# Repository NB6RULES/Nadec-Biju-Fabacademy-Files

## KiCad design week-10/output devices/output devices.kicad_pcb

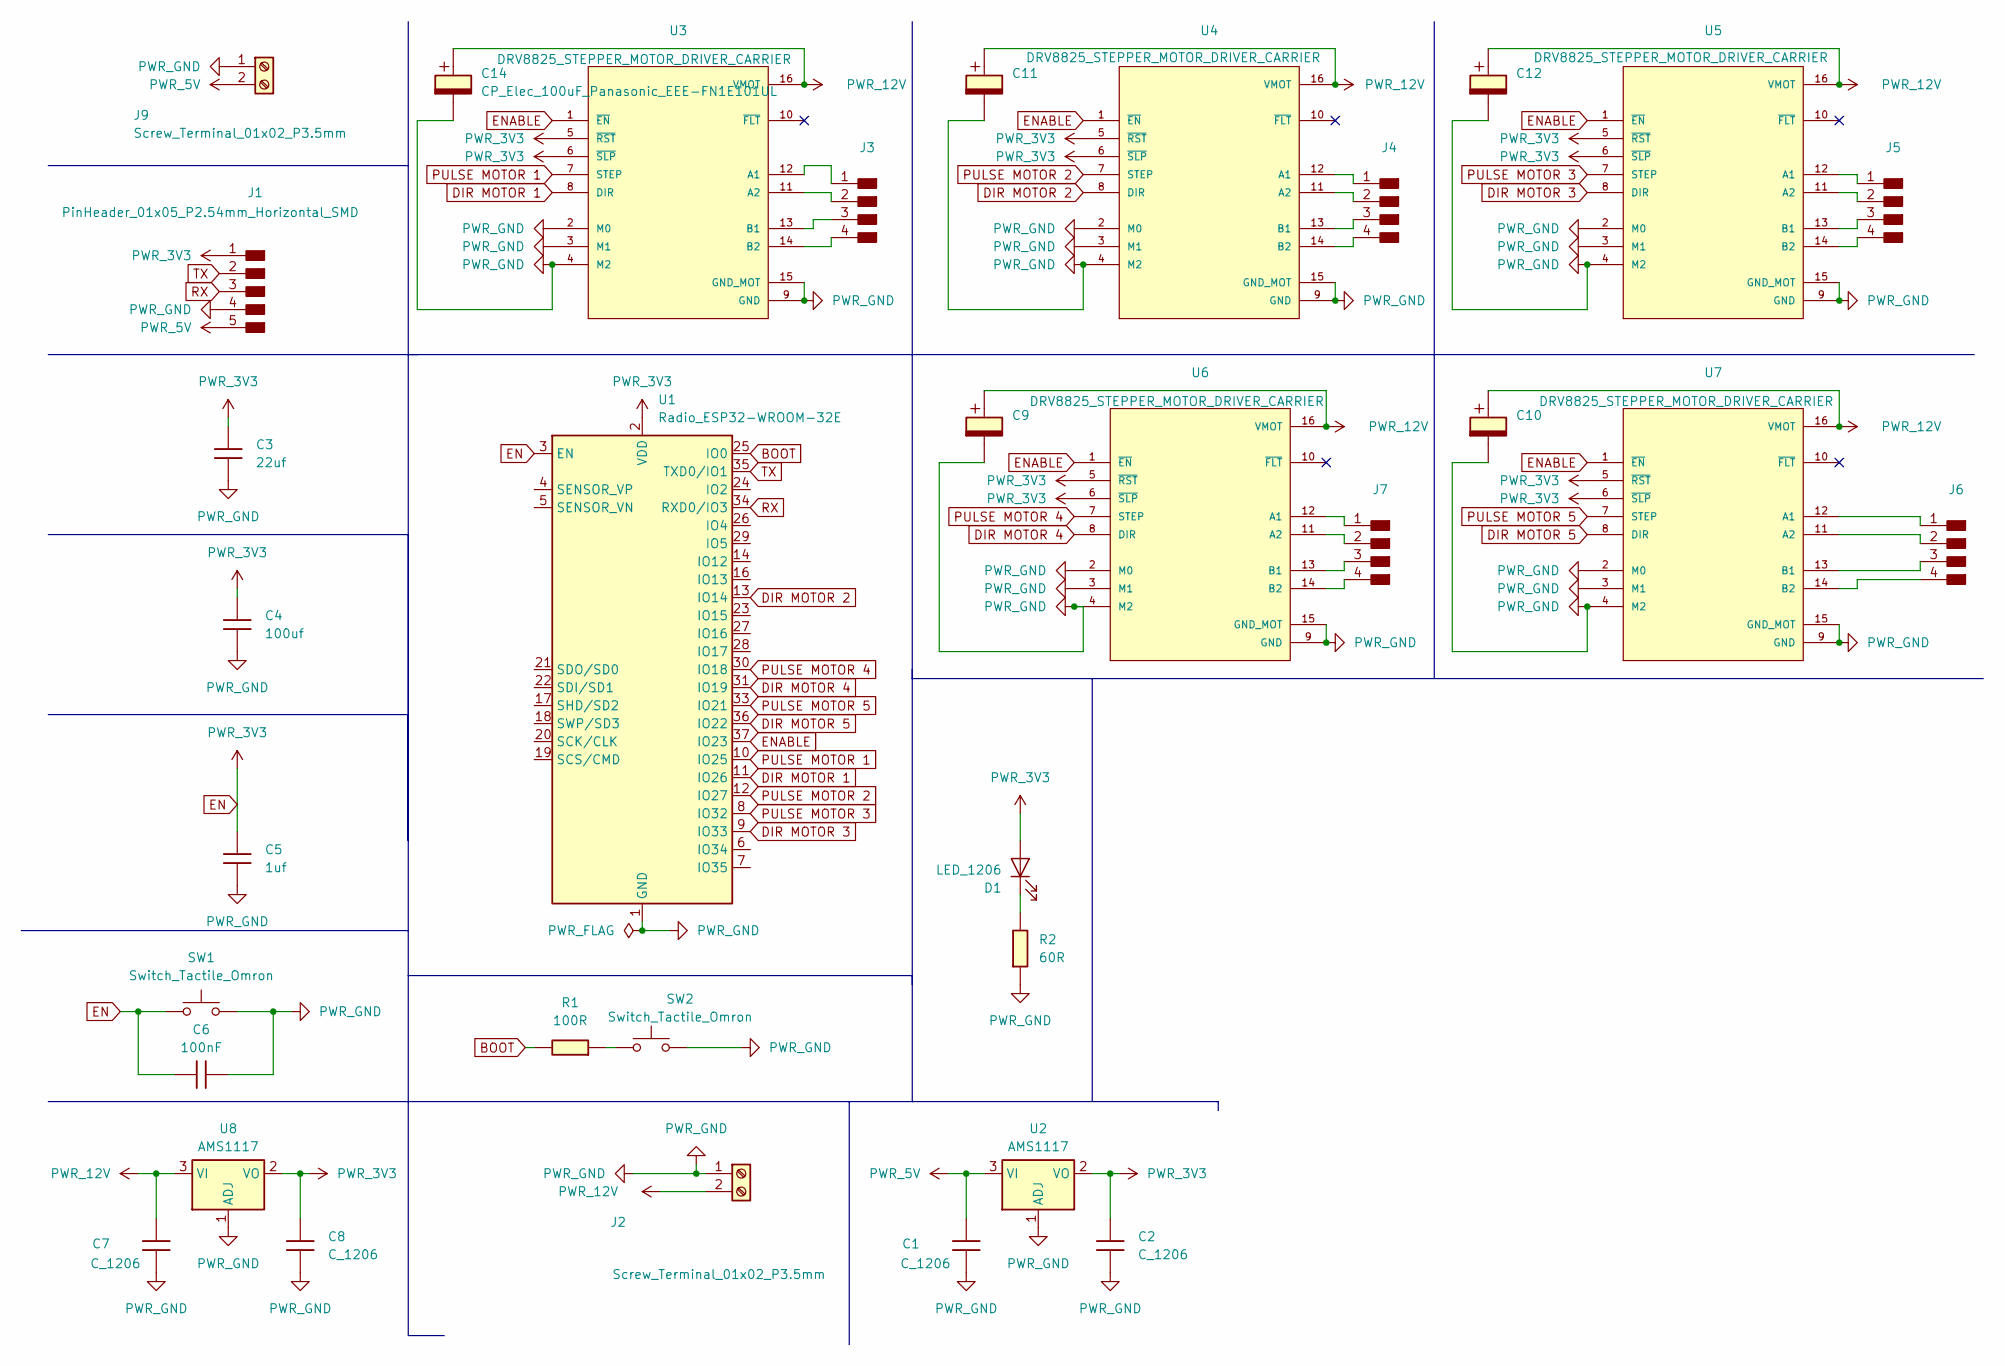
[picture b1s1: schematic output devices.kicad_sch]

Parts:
C1, C2, C7, C8: C_1206
C3: 22uf; C_1206
C4: 100uf; C_1206
C5: 1uf; C_1206
C6: 100nF; C_1206
C9, C10, C11, C12, C14: CP_Elec_100uF_Panasonic_EEE-FN1E101UL; CP_Elec_8x10
D1: LED_1206
J1: PinHeader_01x05_P2.54mm_Horizontal_SMD
J2, J9: Screw_Terminal_01x02_P3.5mm; TerminalBlock_OnShore_1x02_P3.50mm_Horizontal
J3, J4, J5, J6, J7: PinHeader_01x04_P2.54mm_Horizontal_SMD
R1: 100R; R_1206
R2: 60R; R_1206
SW1, SW2: Switch_Tactile_Omron; Button_Omron_B3SN_6.0x6.0mm
U1: Radio_ESP32-WROOM-32E; ESP32-WROOM-32E
U2, U8: AMS1117; SOT-223-3_TabPin2
U3, U4, U5, U6, U7: DRV8825_STEPPER_MOTOR_DRIVER_CARRIER; IC_DRV8825_STEPPER_MOTOR_DRIVER_CARRIER

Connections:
BOOT: R1.1, U1.25 (IO0)
DIR MOTOR 1: U1.11 (IO26), U3.8 (DIR)
DIR MOTOR 2: U1.13 (IO14), U4.8 (DIR)
DIR MOTOR 3: U1.9 (IO33), U5.8 (DIR)
DIR MOTOR 4: U1.31 (IO19), U6.8 (DIR)
DIR MOTOR 5: U1.36 (IO22), U7.8 (DIR)
EN: C2.1, C3.1, C4.1, C5.1, C6.1, C8.1, D1.2 (A), J1.1, SW1.1, U1.2 (VDD), U1.3 (EN), U2.2 (VO), U3.5 (~RST), U3.6 (~SLP), U4.5 (~RST), U4.6 (~SLP), U5.5 (~RST), U5.6 (~SLP), U6.5 (~RST), U6.6 (~SLP), U7.5 (~RST), U7.6 (~SLP), U8.2 (VO)
ENABLE: U1.37 (IO23), U3.1 (~EN), U4.1 (~EN), U5.1 (~EN), U6.1 (~EN), U7.1 (~EN)
unnamed: D1.1 (K), R2.1
unnamed: J3.1, U3.12 (A1)
unnamed: J3.2, U3.11 (A2)
unnamed: J3.3, U3.13 (B1)
unnamed: J3.4, U3.14 (B2)
unnamed: J4.1, U4.12 (A1)
unnamed: J4.2, U4.11 (A2)
unnamed: J4.3, U4.13 (B1)
unnamed: J4.4, U4.14 (B2)
unnamed: J5.1, U5.12 (A1)
unnamed: J5.2, U5.11 (A2)
unnamed: J5.3, U5.13 (B1)
unnamed: J5.4, U5.14 (B2)
unnamed: J6.1, U7.12 (A1)
unnamed: J6.2, U7.11 (A2)
unnamed: J6.3, U7.13 (B1)
unnamed: J6.4, U7.14 (B2)
unnamed: J7.1, U6.12 (A1)
unnamed: J7.2, U6.11 (A2)
unnamed: J7.3, U6.13 (B1)
unnamed: J7.4, U6.14 (B2)
unnamed: R1.2, SW2.1
PULSE MOTOR 1: U1.10 (IO25), U3.7 (STEP)
PULSE MOTOR 2: U1.12 (IO27), U4.7 (STEP)
PULSE MOTOR 3: U1.8 (IO32), U5.7 (STEP)
PULSE MOTOR 4: U1.30 (IO18), U6.7 (STEP)
PULSE MOTOR 5: U1.33 (IO21), U7.7 (STEP)
PWR_5V: C1.1, J1.5, J9.2, U2.3 (VI)
PWR_12V: C7.1, C9.1, C10.1, C11.1, C12.1, C14.1, J2.2, U3.16 (VMOT), U4.16 (VMOT), U5.16 (VMOT), U6.16 (VMOT), U7.16 (VMOT), U8.3 (VI)
PWR_GND: C1.2, C2.2, C3.2, C4.2, C5.2, C6.2, C7.2, C8.2, C9.2, C10.2, C11.2, C12.2, C14.2, J1.4, J2.1, J9.1, R2.2, SW1.2, SW2.2, U1.1 (GND), U1.15 (GND), U1.38 (GND), U1.39 (GND), U2.1 (ADJ), U3.2 (M0), U3.3 (M1), U3.4 (M2), U3.9 (GND), U3.15 (GND_MOT), U4.2 (M0), U4.3 (M1), U4.4 (M2), U4.9 (GND), U4.15 (GND_MOT), U5.2 (M0), U5.3 (M1), U5.4 (M2), U5.9 (GND), U5.15 (GND_MOT), U6.2 (M0), U6.3 (M1), U6.4 (M2), U6.9 (GND), U6.15 (GND_MOT), U7.2 (M0), U7.3 (M1), U7.4 (M2), U7.9 (GND), U7.15 (GND_MOT), U8.1 (ADJ)
RX: J1.3, U1.34 (RXD0/IO3)
TX: J1.2, U1.35 (TXD0/IO1)

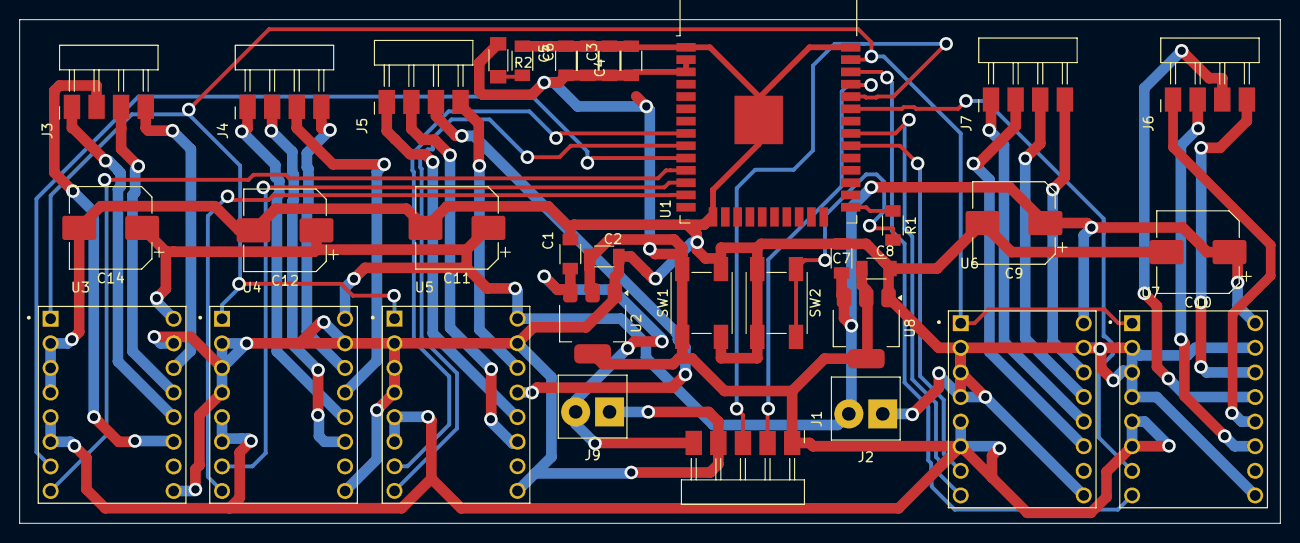
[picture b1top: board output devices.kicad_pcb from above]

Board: 2 copper layers, 130.2 x 52.0 mm, 34 parts (0 on the bottom side), 40 nets.

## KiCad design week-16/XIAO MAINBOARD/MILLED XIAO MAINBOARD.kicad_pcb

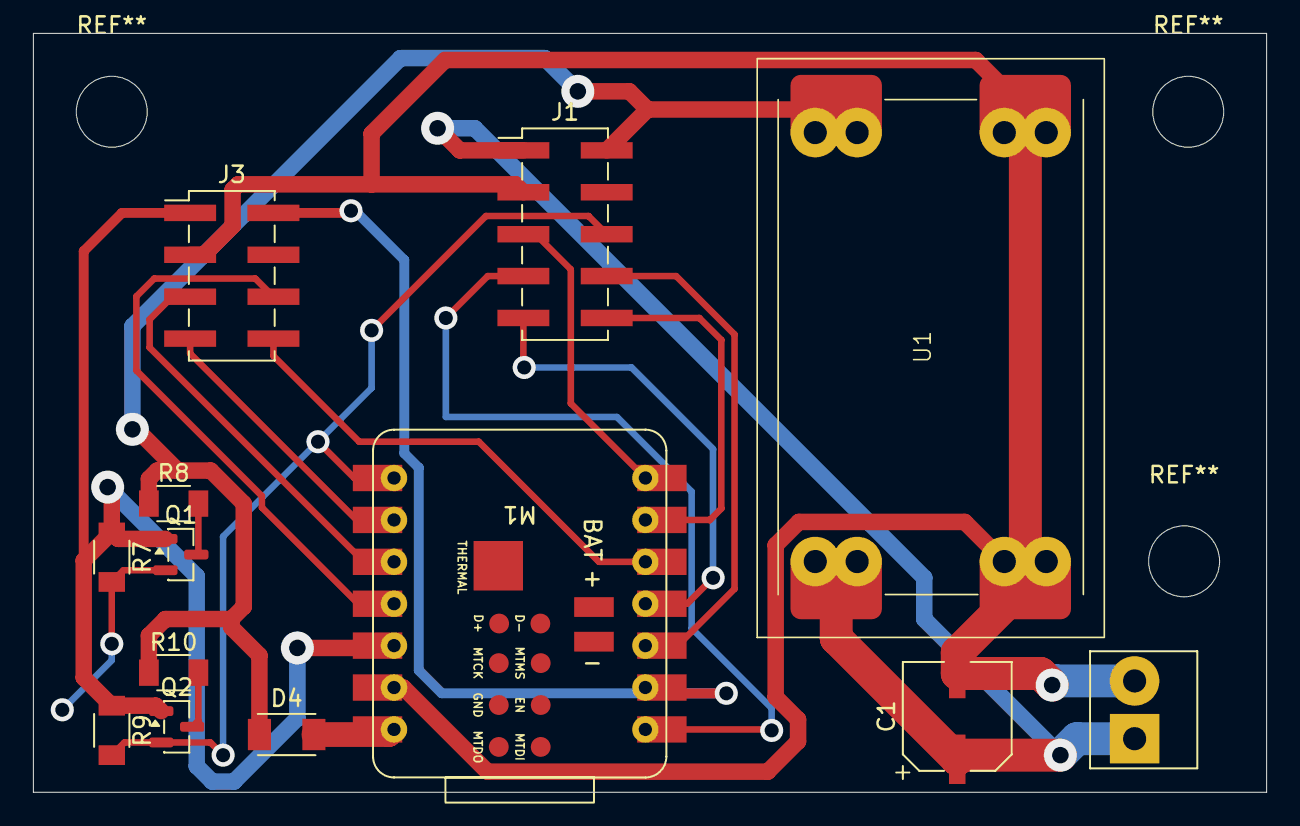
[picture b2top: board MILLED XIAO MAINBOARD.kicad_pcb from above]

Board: 2 copper layers, 74.8 x 46.0 mm, 13 parts (0 on the bottom side), 19 nets.

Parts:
C1: CP_Elec_100uF; CP_Elec_100uF_Panasonic_EEE-FN1E101UL
D4: Diode_Schottky_MiniSMA
J1: PinHeader_02x05_P2.54mm_Vertical_SMD
J2: Screw_Terminal_01x02_P3.5mm; TerminalBlock_OnShore_1x02_P3.50mm_Horizontal
J3: PinHeader_02x04_P2.54mm_Vertical_SMD
M1: Module_XIAO-ESP32S3; SeeedStudio_XIAO_ESP32S3
Q1, Q2: BSS138; SOT-23
R7, R8, R9, R10: 10K; R_1206
U1: Mini560_DCDC_Buck_module

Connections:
3.3v: J3.1, M1.12 (3V3), Q1.1 (G), Q2.1 (G), R7.1, R9.1
5v: D4.2 (A), J1.2, R8.1, R10.1, U1.3 (OUT+)
12v: C1.1, J1.1, J2.1, U1.1 (IN+)
DRAW 1 DIN: Q1.3 (D), R8.2
GND: C1.2, J1.3, J2.2, J3.3, M1.13 (GND), U1.2 (IN-), U1.4 (OUT-)
HALL EFFECT 3 OUT: Q2.3 (D), R10.2
MISO: J3.5, M1.10 (D9)
MOSI: J3.6, M1.11 (D10)
NEOPIXEL DATA: J1.7, M1.1 (D0)
unnamed: D4.1 (K), M1.14 (5V)
RST: J3.2, M1.2 (D1)
RX - BUTTON DOUT: J1.6, M1.8 (D7), Q2.2 (S), R9.2
SCK: J3.7, M1.9 (D8)
SDA: J3.8, M1.5 (D4)
Solenoid 1 Control: J1.8, M1.3 (D2)
Solenoid 2 Control: J1.9, M1.4 (D3)
Solenoid 3 Control: J1.10, M1.6 (D5)
TX - BUTTON DIN: J1.5, M1.7 (D6)
TX - BUTTON DOUT: Q1.2 (S), R7.2

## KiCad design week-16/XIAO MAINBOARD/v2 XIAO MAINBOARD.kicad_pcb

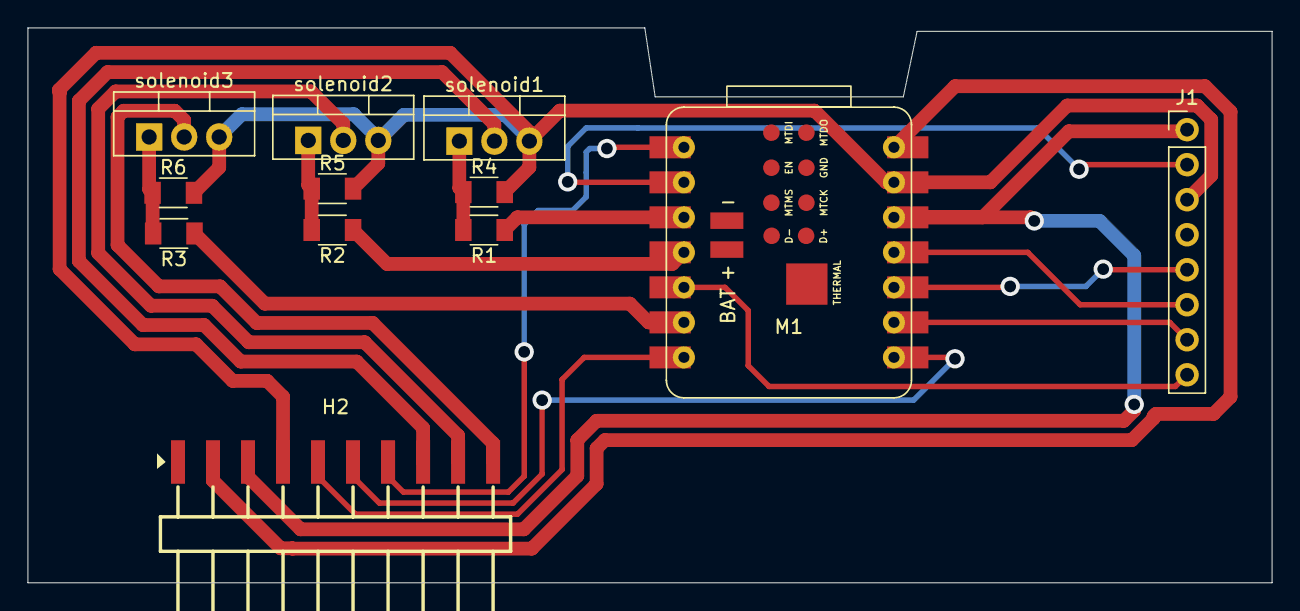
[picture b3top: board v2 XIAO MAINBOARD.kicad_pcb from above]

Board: 2 copper layers, 90.2 x 40.2 mm, 12 parts (0 on the bottom side), 20 nets.

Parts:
H2: HX PZ2.54-1X10P WT; HDR-SMD_10P-P2.54-H-M-W13.3-N
J1: PinHeader_01x08_P2.54mm_Vertical_THT_D1mm
M1: Module_XIAO-ESP32S3; SeeedStudio_XIAO_ESP32S3
R1, R2, R3: 1K; R_1206
R4, R5, R6: 10K; R_1206
solenoid1, solenoid2, solenoid3: IRLZ44N; TO-220-3_Vertical

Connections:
3.3v: H2.3, J1.1, M1.12 (3V3)
5v: H2.2, M1.14 (5V)
GND: H2.4, J1.3, M1.13 (GND), R4.2, R5.2, R6.2, solenoid1.3 (S), solenoid2.3 (S), solenoid3.3 (S)
MISO: J1.5, M1.10 (D9)
MOSI: J1.6, M1.11 (D10)
NEOPIXEL DATA: H2.7, M1.1 (D0)
unnamed: R1.2, R4.1, solenoid1.1 (G)
unnamed: R2.2, R5.1, solenoid2.1 (G)
unnamed: R3.2, R6.1, solenoid3.1 (G)
RST: J1.2, M1.2 (D1)
RX - BUTTON DOUT: H2.6, M1.8 (D7)
SCK: J1.7, M1.9 (D8)
SDA: J1.8, M1.5 (D4)
Solenoid 1: H2.8, solenoid1.2 (D)
Solenoid 1 Control: M1.3 (D2), R1.1
Solenoid 2: H2.9, solenoid2.2 (D)
Solenoid 2 Control: M1.4 (D3), R2.1
Solenoid 3: H2.10, solenoid3.2 (D)
Solenoid 3 Control: M1.6 (D5), R3.1
TX - BUTTON DIN: H2.5, M1.7 (D6)

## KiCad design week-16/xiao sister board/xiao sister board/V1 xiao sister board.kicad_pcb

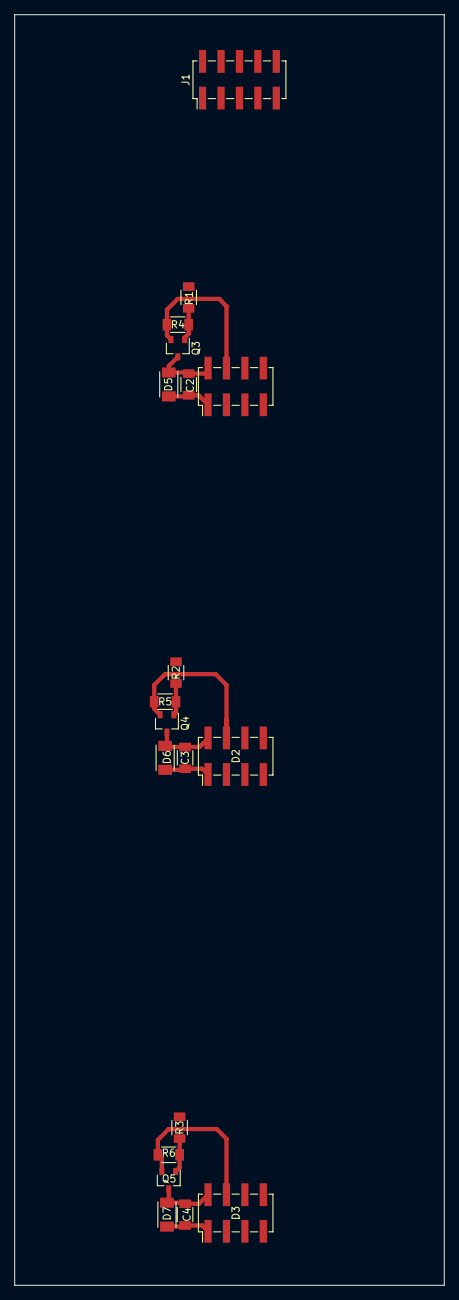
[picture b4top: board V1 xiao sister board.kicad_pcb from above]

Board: 2 copper layers, 59.2 x 175.2 mm, 19 parts (0 on the bottom side), 18 nets.

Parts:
C2, C3, C4: 100nf; C_1206
D1: DRAW 1; PinHeader_02x04_P2.54mm_Vertical_SMD
D2: DRAW 2; PinHeader_02x04_P2.54mm_Vertical_SMD
D3: DRAW 3; PinHeader_02x04_P2.54mm_Vertical_SMD
D5, D6, D7: Diode_Schottky_MiniSMA
J1: PinHeader_02x05_P2.54mm_Vertical_SMD
Q3, Q4, Q5: Transistor_MOSFET_NCh_SOT23; SOT-23-3
R1, R2, R3: 1K; R_1206
R4, R5, R6: 10K; R_1206

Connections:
5v: D1.3, D2.3, D3.3, J1.2
12v: C2.2, C3.2, C4.2, D1.1, D2.1, D3.1, D5.1 (K), D6.1 (K), D7.1 (K), J1.1
DRAW 1 DOUT: D1.6, D2.5
GND: D1.4, D2.4, D3.4, J1.3, Q3.2 (S), Q4.2 (S), Q5.2 (S), R4.2, R5.2, R6.2
NEOPIXEL DATA: D1.7, J1.7
NEOPIXEL DATA OUT 1: D1.8, D2.7
NEOPIXEL DATA OUT 2: D2.8, D3.7
unnamed: Q3.1 (G), R1.2, R4.1
unnamed: Q4.1 (G), R2.2, R5.1
unnamed: Q5.1 (G), R3.2, R6.1
RX - BUTTON DOUT: D3.8, J1.6
Solenoid 1: C2.1, D1.2, D5.2 (A), Q3.3 (D)
Solenoid 1 Control: J1.8, R1.1
Solenoid 2: C3.1, D2.2, D6.2 (A), Q4.3 (D)
Solenoid 2 Control: J1.9, R2.1
Solenoid 3: C4.1, D3.2, D7.2 (A), Q5.3 (D)
Solenoid 3 Control: J1.10, R3.1
TX - BUTTON DIN: D1.5, J1.5

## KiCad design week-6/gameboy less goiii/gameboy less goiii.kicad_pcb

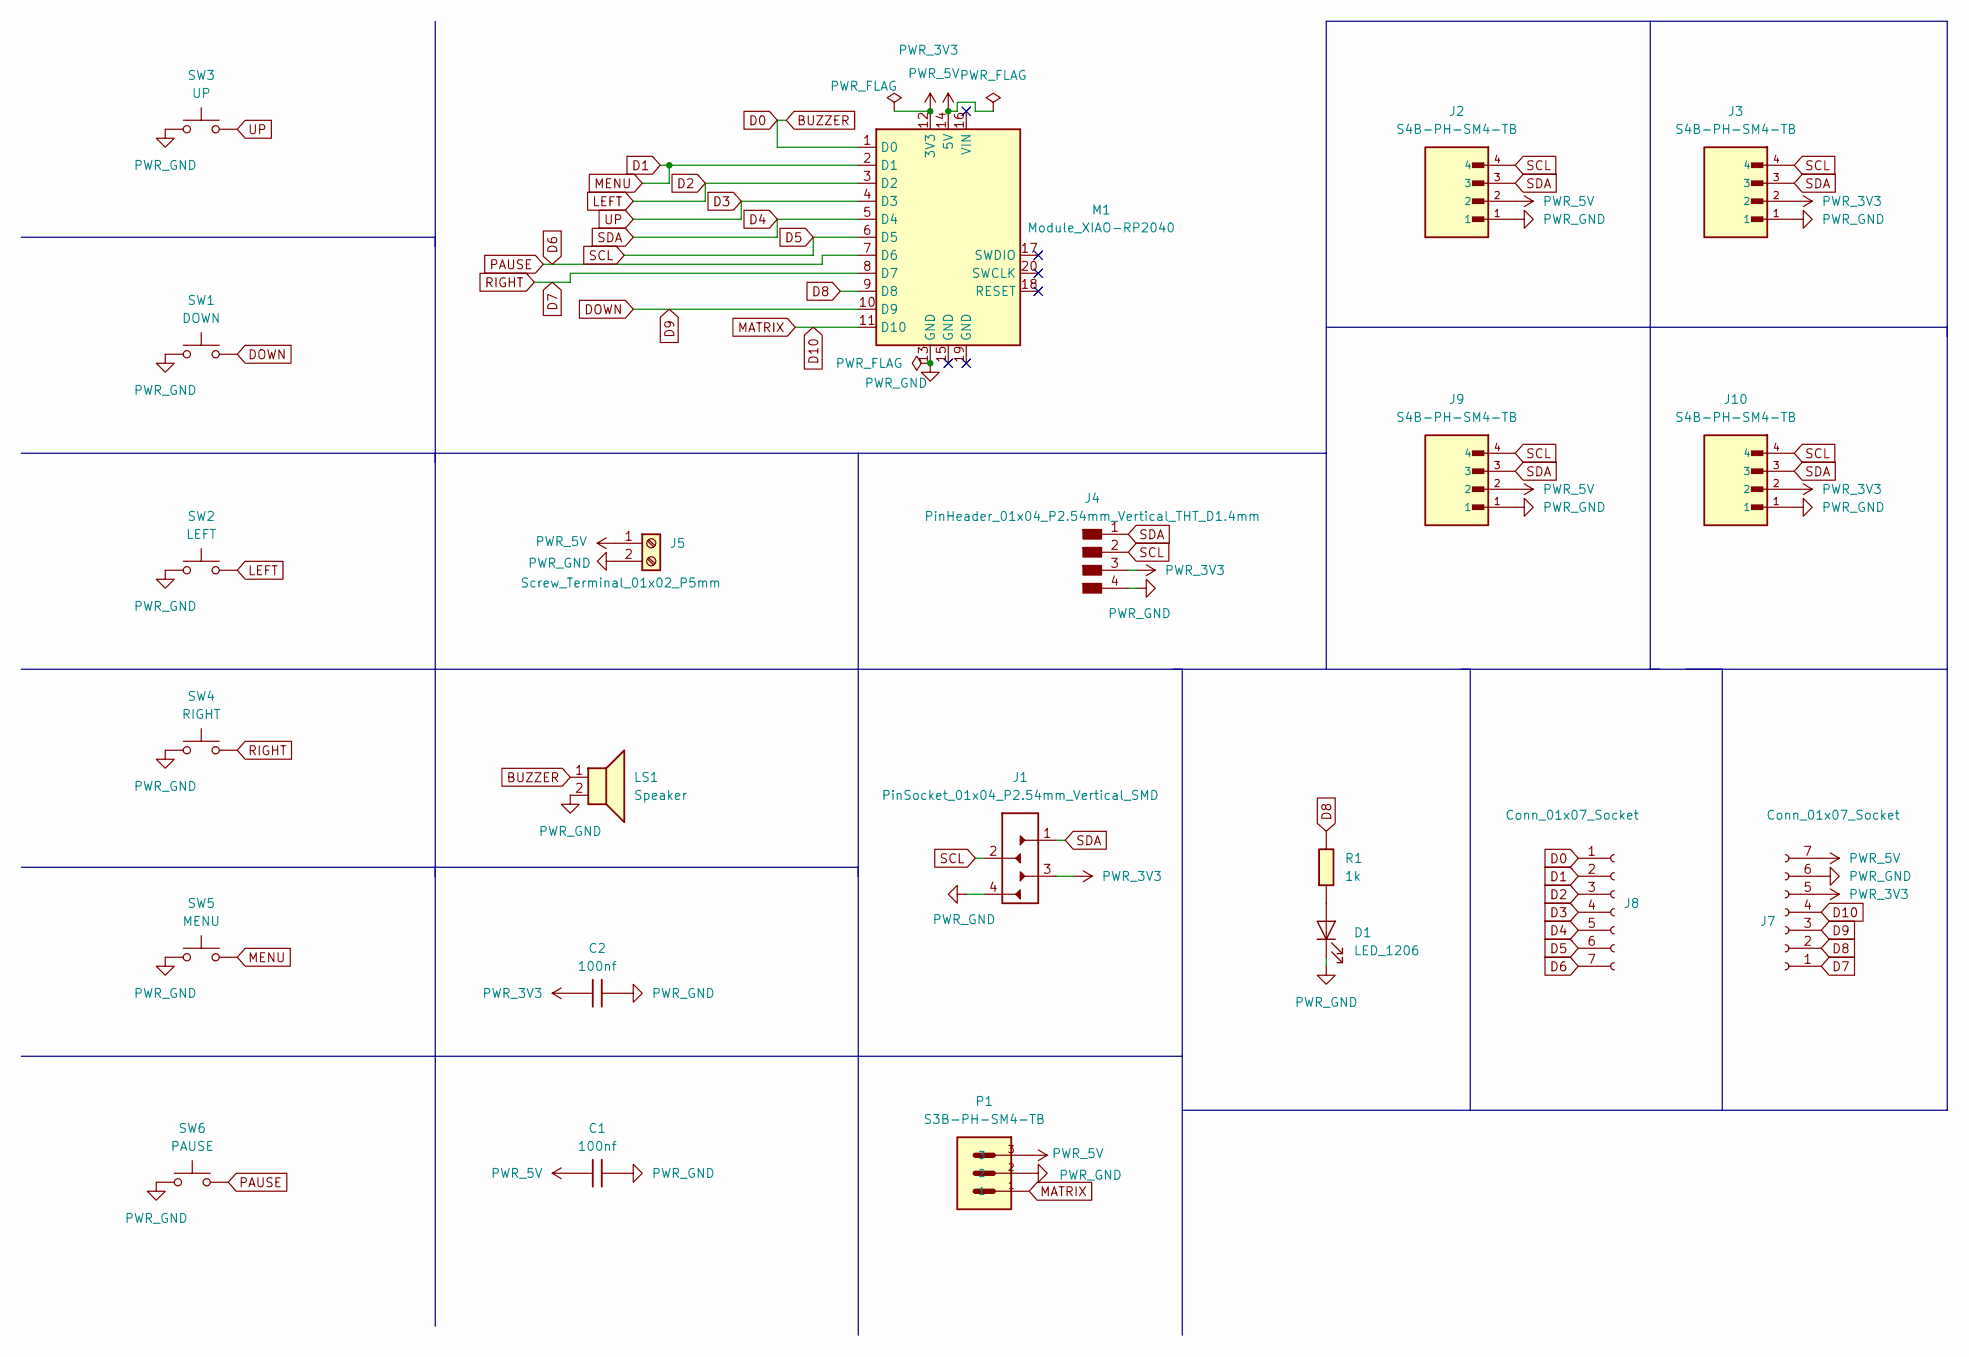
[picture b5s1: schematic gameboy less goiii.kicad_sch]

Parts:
C1, C2: 100nf; C_1206
D1: LED_1206
J1: PinSocket_01x04_P2.54mm_Vertical_SMD
J2, J3, J9, J10: S4B-PH-SM4-TB; JST_S4B-PH-SM4-TB
J4: PinHeader_01x04_P2.54mm_Vertical_THT_D1.4mm
J5: Screw_Terminal_01x02_P5mm; TerminalBlock_OnShore_1x02_P5.00mm_Horizontal
J7, J8: Conn_01x07_Socket; PinSocket_1x07_P2.54mm_Vertical_SMD_Pin1Right
LS1: Speaker; PinHeader_01x02_P2.54mm_Horizontal_SMD
M1: Module_XIAO-RP2040; SeeedStudio_XIAO_RP2040
P1: S3B-PH-SM4-TB; JST_S3B-PH-SM4-TB
R1: 1k; R_1206
SW1: DOWN; Button_Omron_B3SN_6.0x6.0mm
SW2: LEFT; Button_Omron_B3SN_6.0x6.0mm
SW3: UP; Button_Omron_B3SN_6.0x6.0mm
SW4: RIGHT; Button_Omron_B3SN_6.0x6.0mm
SW5: MENU; Button_Omron_B3SN_6.0x6.0mm
SW6: PAUSE; Button_Omron_B3SN_6.0x6.0mm

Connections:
BUZZER: J8.1, LS1.1, M1.1 (D0)
D1: J8.2, M1.2 (D1), SW5.2
D2: J8.3, M1.3 (D2), SW2.2
D3: J8.4, M1.4 (D3), SW3.2
D4: J1.1, J2.3, J3.3, J4.1, J8.5, J9.3, J10.3, M1.5 (D4)
D5: J1.2, J2.4, J3.4, J4.2, J8.6, J9.4, J10.4, M1.6 (D5)
D6: J8.7, M1.7 (D6), SW6.2
D7: J7.1, M1.8 (D7), SW4.2
D8: J7.2, M1.9 (D8), R1.1
D9: J7.3, M1.10 (D9), SW1.2
D10: J7.4, M1.11 (D10), P1.1
unnamed: D1.2 (A), R1.2
PWR_3V3: C2.1, J1.3 (Pin_1), J3.2, J4.3, J7.5, J10.2, M1.12 (3V3)
PWR_5V: C1.1, J2.2, J5.1, J7.7, J9.2, M1.14 (5V), P1.3
PWR_GND: C1.2, C2.2, D1.1 (K), J1.4 (Pin_2), J2.1, J3.1, J4.4, J5.2, J7.6, J9.1, J10.1, LS1.2, M1.13 (GND), P1.2, SW1.1, SW2.1, SW3.1, SW4.1, SW5.1, SW6.1

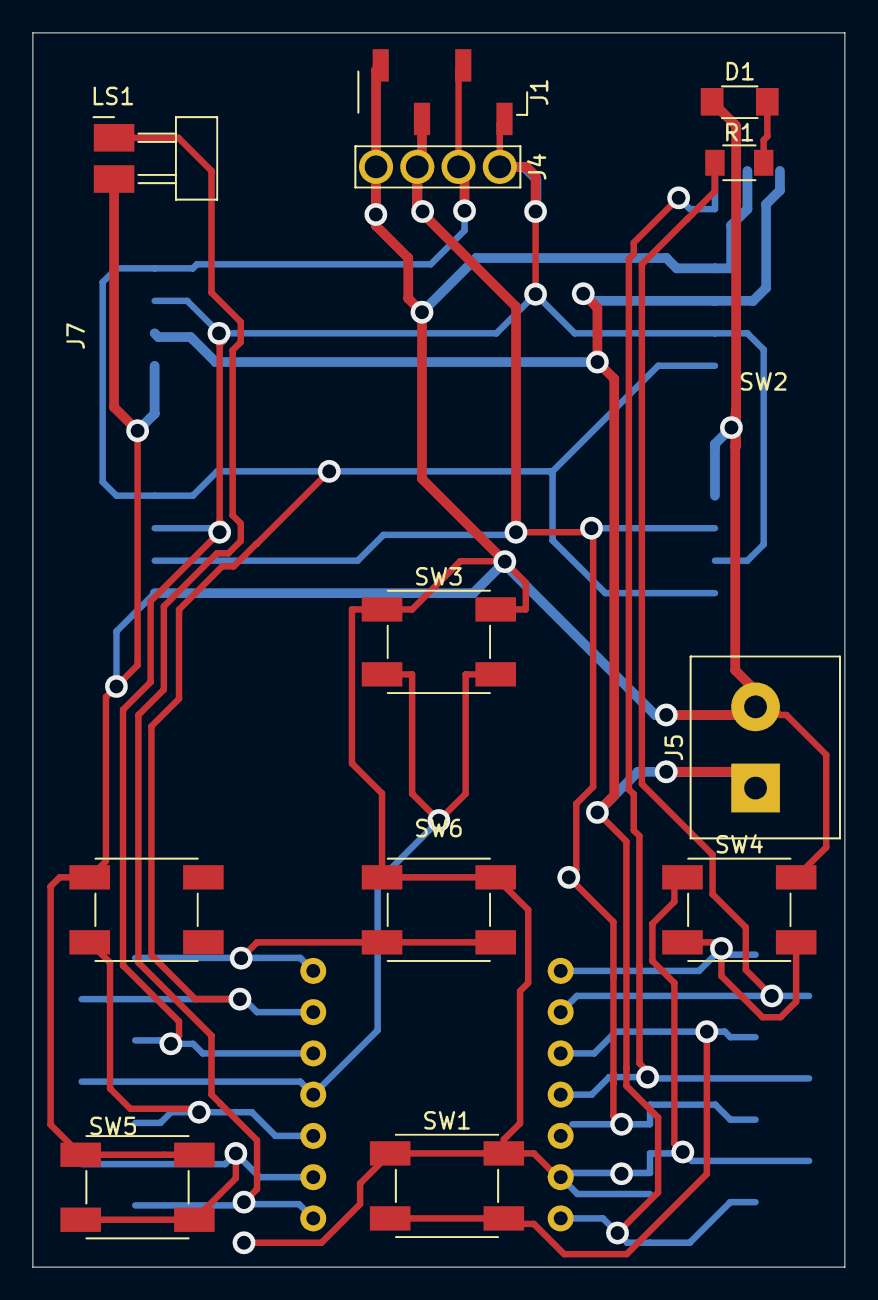
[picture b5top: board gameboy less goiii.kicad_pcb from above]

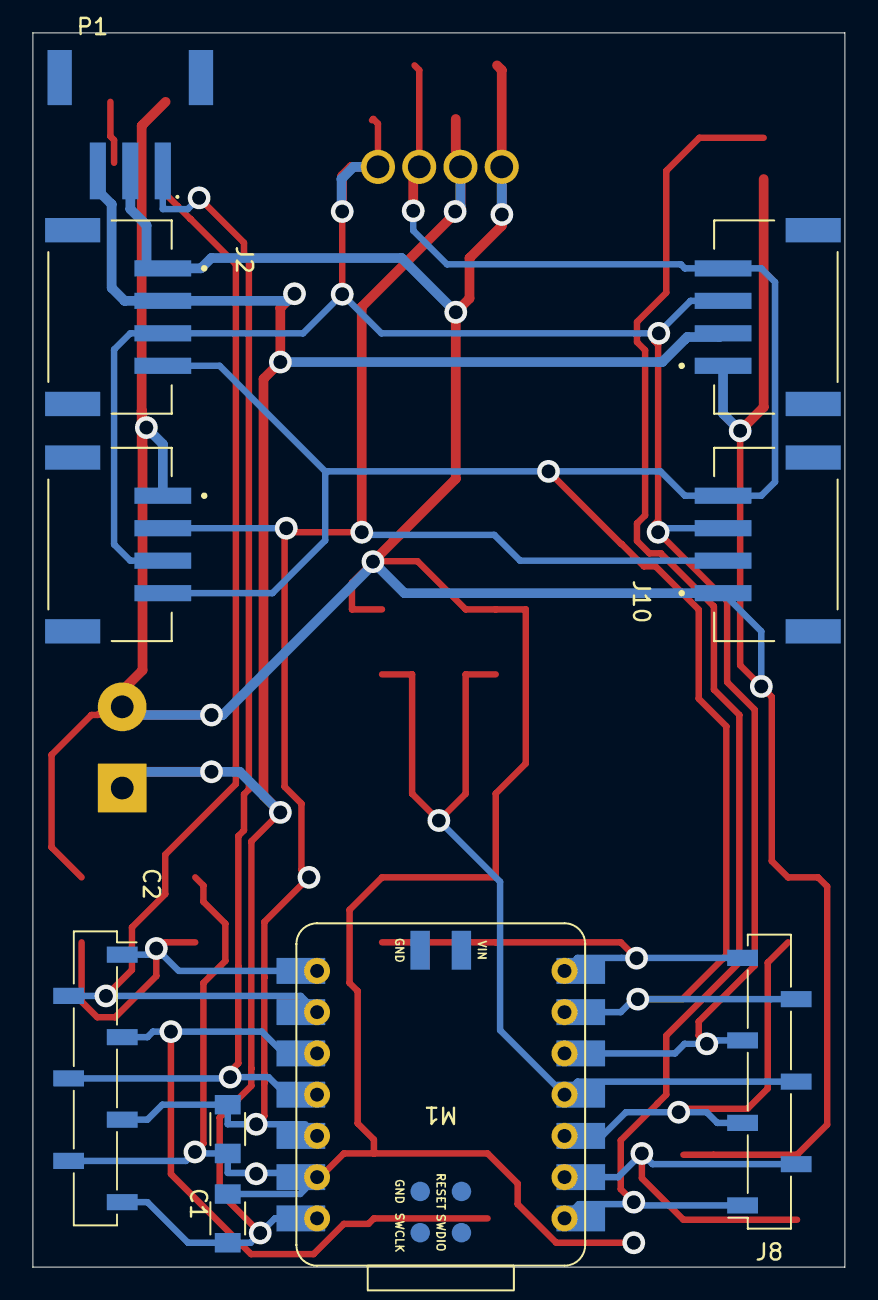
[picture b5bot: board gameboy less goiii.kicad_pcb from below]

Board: 2 copper layers, 50.0 x 76.0 mm, 22 parts (10 on the bottom side), 15 nets.

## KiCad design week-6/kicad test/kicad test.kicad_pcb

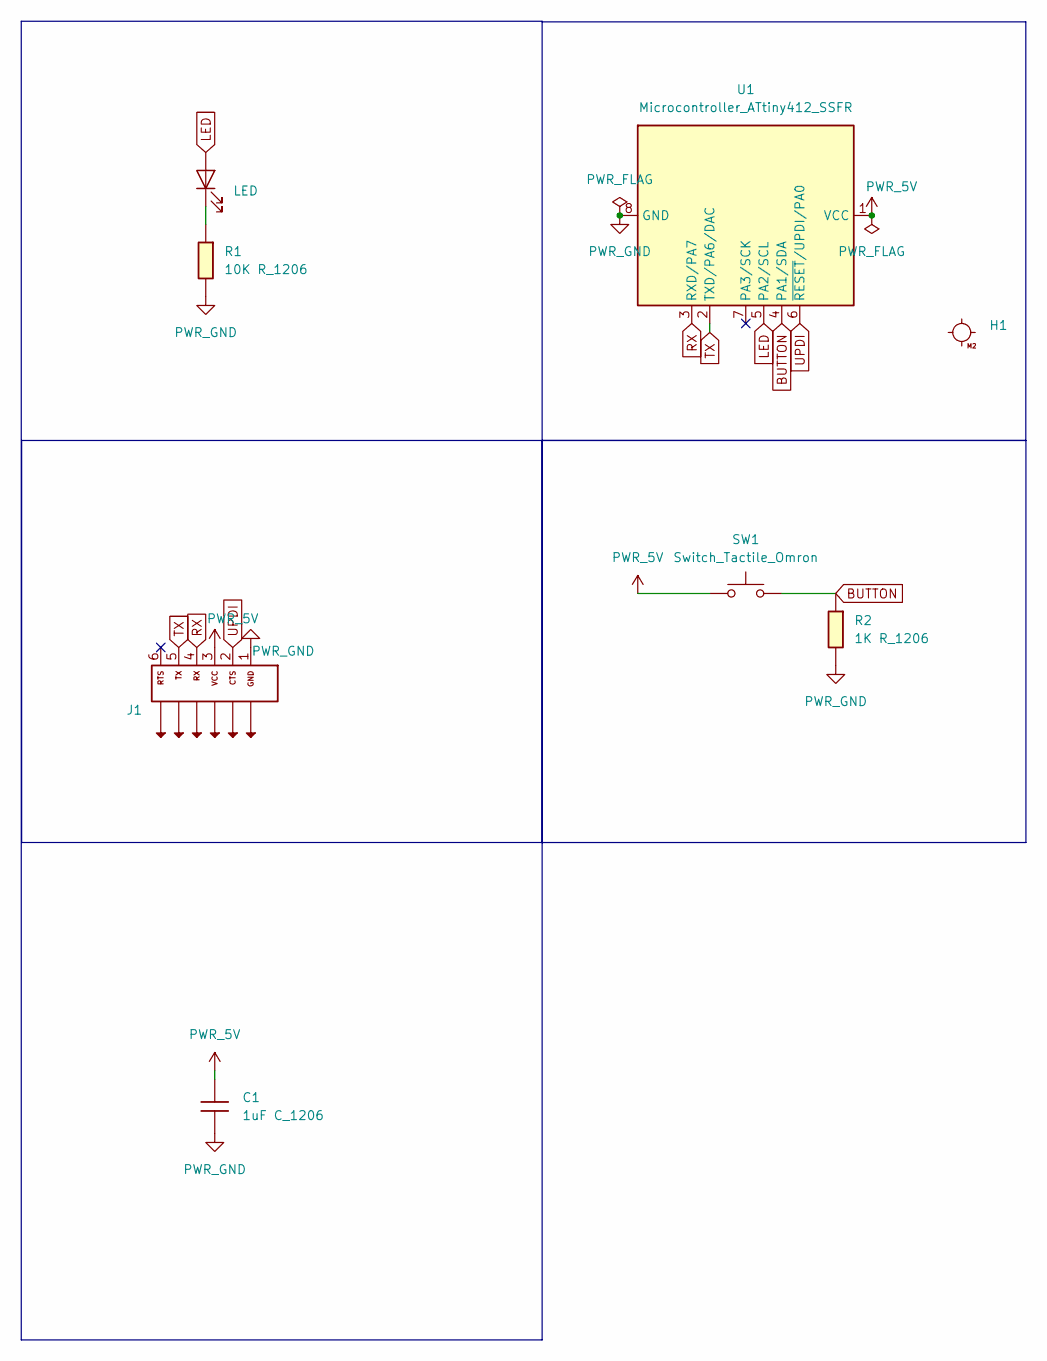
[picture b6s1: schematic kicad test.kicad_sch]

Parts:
C1: 1uF C_1206; C_1206
D1: LED; LED_1206
H1: MountingHole_M2
J1: Conn_PinHeader_FTDI_1x06_P2.54mm_Horizontal_SMD; PinHeader_01x06_P2.54mm_Horizontal_SMD
R1: 10K R_1206; R_1206
R2: 1K R_1206; R_1206
SW1: Switch_Tactile_Omron; Button_Omron_B3SN_6.0x6.0mm
U1: Microcontroller_ATtiny412_SSFR; SOIC-8_3.9x4.9mm_P1.27mm

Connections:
BUTTON: R2.2, SW1.2, U1.4 (PA1/SDA)
LED: D1.2 (A), U1.5 (PA2/SCL)
unnamed: D1.1 (K), R1.2
PWR_5V: C1.1, J1.3, SW1.1, U1.1 (VCC)
PWR_GND: C1.2, J1.1, R1.1, R2.1, U1.8 (GND)
RX: J1.4, U1.3 (RXD/PA7)
TX: J1.5, U1.2 (TXD/PA6/DAC)
UPDI: J1.2, U1.6 (~RESET/UPDI/PA0)

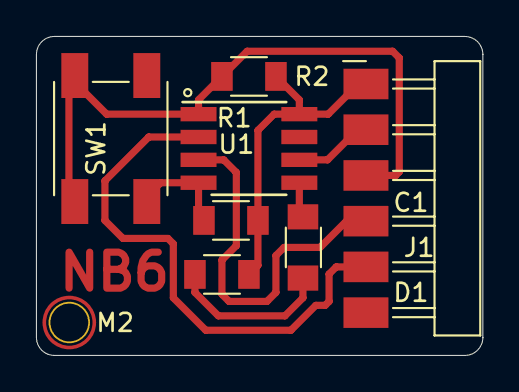
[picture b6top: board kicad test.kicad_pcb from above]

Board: 2 copper layers, 24.8 x 17.7 mm, 8 parts (0 on the bottom side), 8 nets.

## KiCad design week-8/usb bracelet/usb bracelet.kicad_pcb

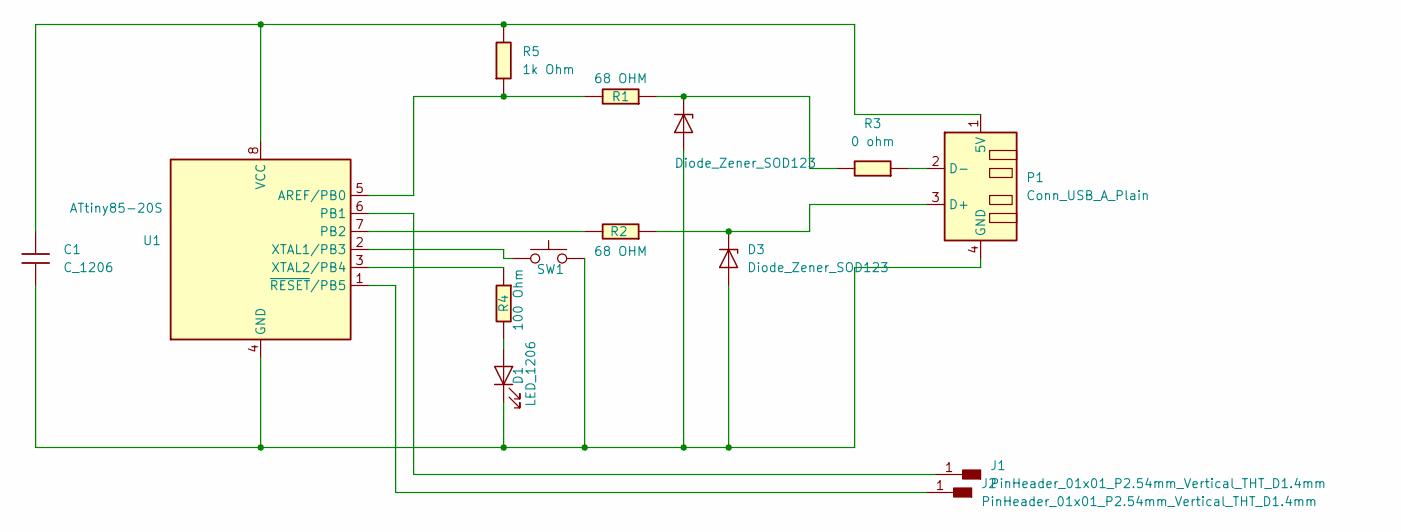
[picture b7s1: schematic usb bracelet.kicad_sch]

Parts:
C1: C_1206
D1: LED_1206
D2, D3: Diode_Zener_SOD123; SOD-123
J1, J2: PinHeader_01x01_P2.54mm_Vertical_THT_D1.4mm
P1: Conn_USB_A_Plain
R1, R2: 68 OHM; R_1206
R3: 0 ohm; R_1206
R4: 100 Ohm; R_1206
R5: 1k Ohm; R_1206
SW1: Switch_Tactile_CUIDevices; Button_CUIDevices_TS04-66-43-BK-260-SMT_6.0x6.0mm
U1: ATtiny85-20S; SOIC-8_5.3x5.3mm_P1.27mm

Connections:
unnamed: D1.2 (A), R4.1
unnamed: C1.2, D1.1 (K), D2.2 (A), D3.2 (A), P1.4 (GND), SW1.3, SW1.4, U1.4 (GND)
unnamed: D2.1 (K), R1.2, R3.1
unnamed: D3.1 (K), P1.3 (D+), R2.2
unnamed: J1.1, U1.6 (PB1)
unnamed: J2.1, U1.1 (~RESET/PB5)
unnamed: C1.1, P1.1 (5V), R5.1, U1.8 (VCC)
unnamed: P1.2 (D-), R3.2
unnamed: R1.1, R5.2, U1.5 (AREF/PB0)
unnamed: R2.1, U1.7 (PB2)
unnamed: SW1.1, SW1.2, U1.2 (XTAL1/PB3)
unnamed: R4.2, U1.3 (XTAL2/PB4)

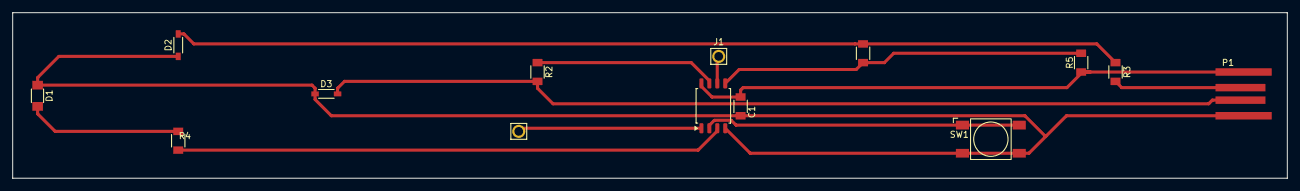
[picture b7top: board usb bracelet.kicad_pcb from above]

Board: 2 copper layers, 204.0 x 26.5 mm, 14 parts (0 on the bottom side), 12 nets.
